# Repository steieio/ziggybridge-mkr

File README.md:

# Ziggy Bridge MKR

This is an adapter for boards in the Arduino MKR form factor, like some of the great low-cost FPGA boards from Trenz.

All of the 100mil pitch connectors use staggered footprints for friction fit so you can use the board without soldering.

This board adapts the MKR dual inline headers to the following connection standards:

 * 2x PMOD
 * mikroBUS Click
 * qwiic/Stemma-QT
 * Raspberry Pi UART

One of the PMOD connectors is issolated on pins D0-D7, the other is connected in parallel with the click/qwiic/uart connectors.

[Click here to view in Kicanvas](https://kicanvas.org/?github=https%3A%2F%2Fgithub.com%2Fsteieio%2Fziggybridge-mkr)

[Click here to purchase from OSH Park](https://oshpark.com/shared_projects/fBhDnFxY)

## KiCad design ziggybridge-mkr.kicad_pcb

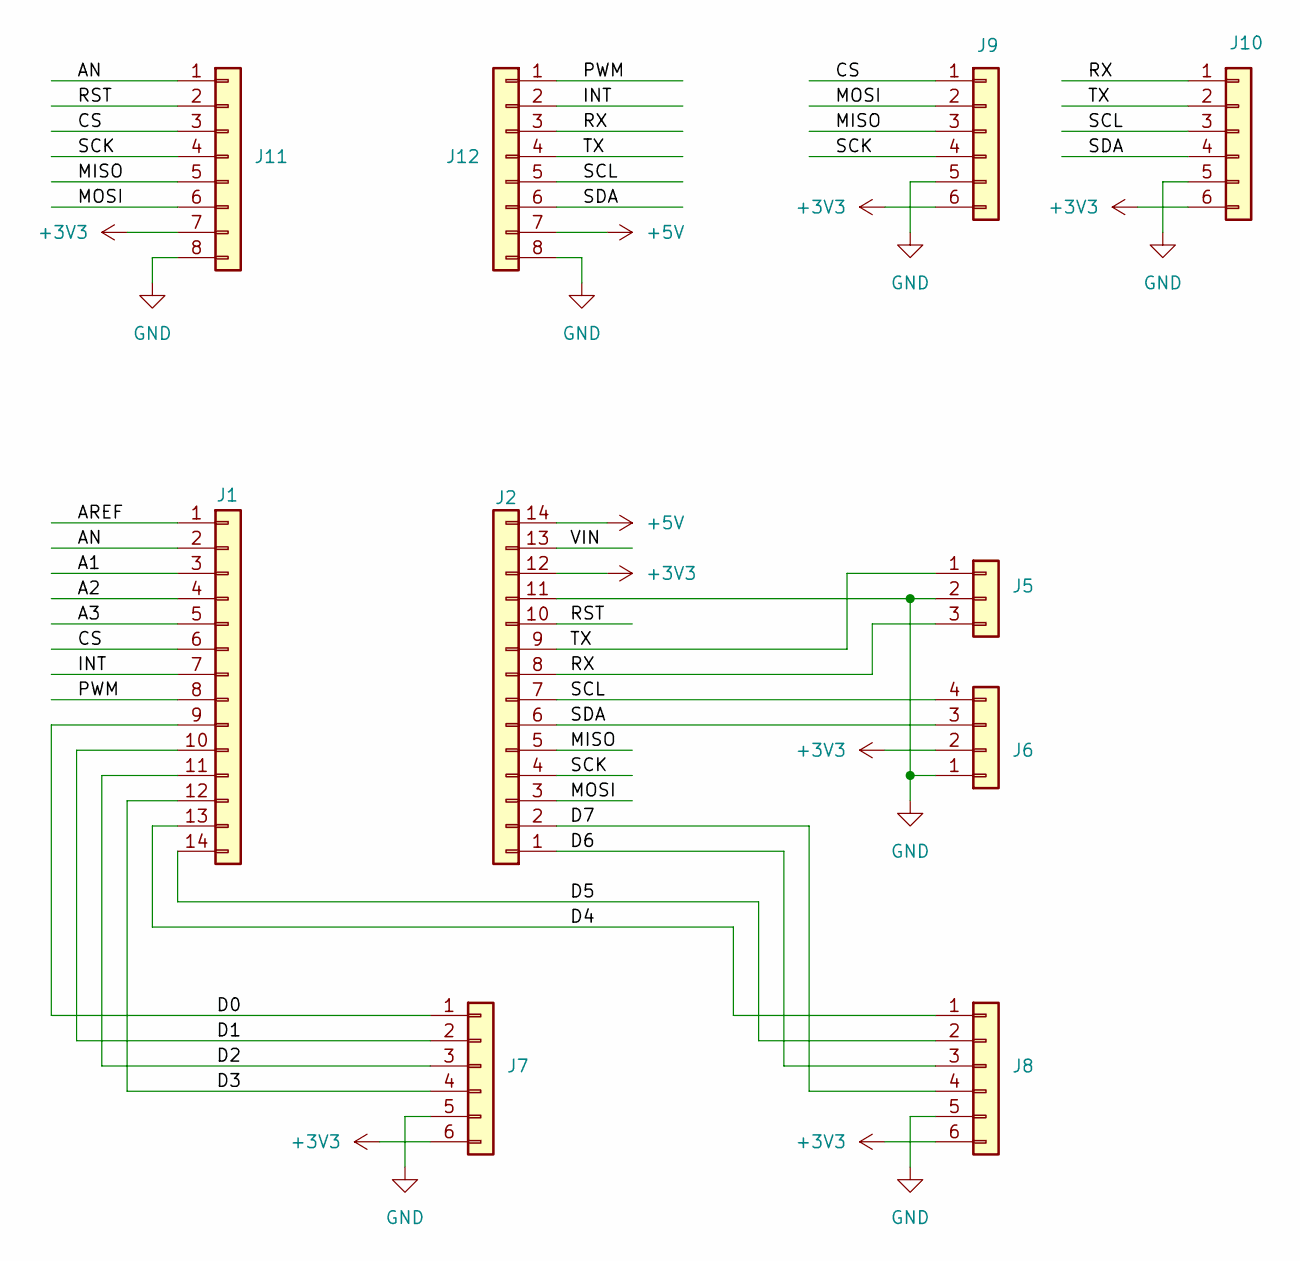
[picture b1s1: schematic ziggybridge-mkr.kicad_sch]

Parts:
J1, J2: Conn_01x14; PinHeader_1x14_P2.54mm_Staggered
J5: Conn_01x03; JST_SH_SM03B-SRSS-TB_1x03-1MP_P1.00mm_Horizontal
J6: Conn_01x04; JST_SH_SM04B-SRSS-TB_1x04-1MP_P1.00mm_Horizontal
J7, J8, J9, J10: Conn_01x06; PinHeader_1x06_P2.54mm_Staggered
J11, J12: Conn_01x08; PinHeader_1x08_P2.54mm_Staggered

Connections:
+3V3: J2.12, J6.2, J7.6, J8.6, J9.6, J10.6, J11.7
+5V: J2.14, J12.7
/A1: J1.3
/A2: J1.4
/A3: J1.5
/AN: J1.2, J11.1
/AREF: J1.1
/CS: J1.6, J9.1, J11.3
/D0: J1.9, J7.1
/D1: J1.10, J7.2
/D2: J1.11, J7.3
/D3: J1.12, J7.4
/D4: J1.13, J8.1
/D5: J1.14, J8.2
/D6: J2.1, J8.3
/D7: J2.2, J8.4
/INT: J1.7, J12.2
/MISO: J2.5, J9.3, J11.5
/MOSI: J2.3, J9.2, J11.6
/PWM: J1.8, J12.1
/RST: J2.10, J11.2
/RX: J2.8, J5.3, J10.1, J12.3
/SCK: J2.4, J9.4, J11.4
/SCL: J2.7, J6.4, J10.3, J12.5
/SDA: J2.6, J6.3, J10.4, J12.6
/TX: J2.9, J5.1, J10.2, J12.4
/VIN: J2.13
GND: J2.11, J5.2, J6.1, J7.5, J8.5, J9.5, J10.5, J11.8, J12.8

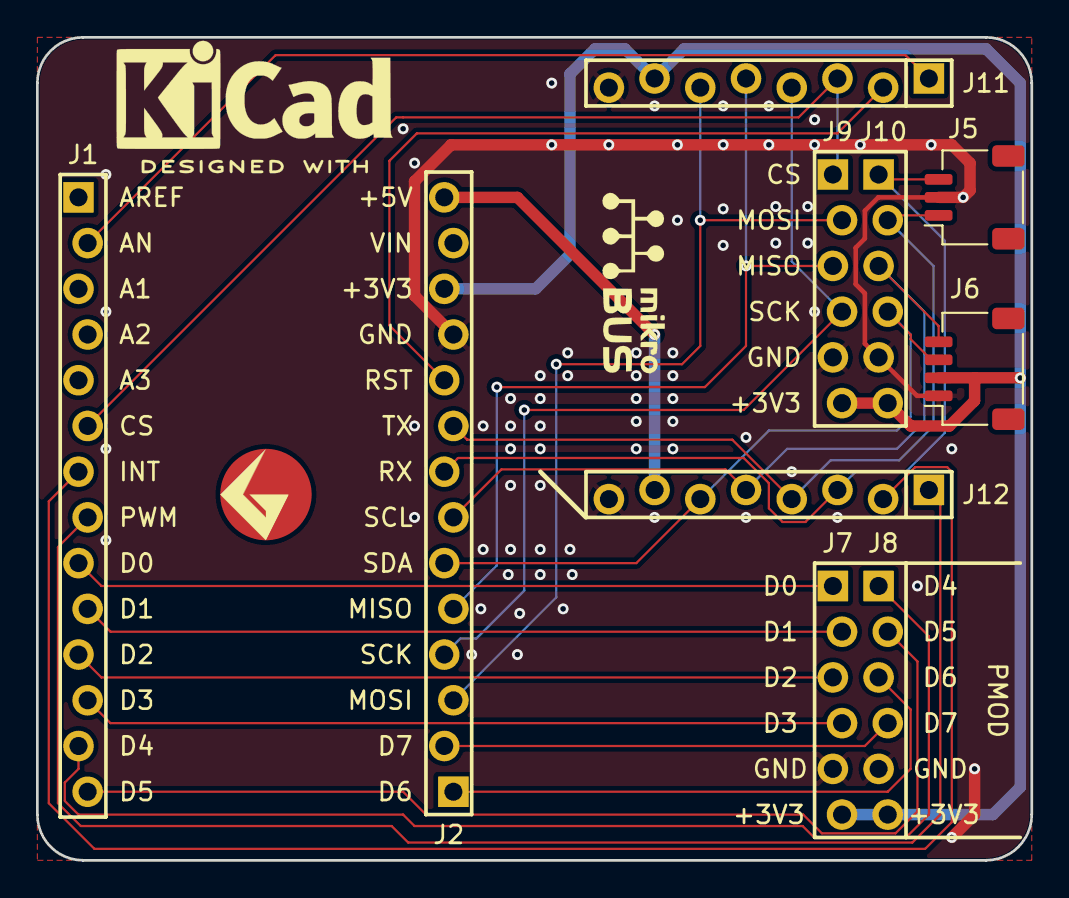
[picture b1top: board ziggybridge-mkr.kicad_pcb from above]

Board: 2 copper layers, 55.2 x 45.7 mm, 11 parts (0 on the bottom side), 23 nets.

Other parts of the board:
GS1: GS_logo; gs_logo_200mil

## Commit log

2025-07-30 chekcing in fully routed board
2025-07-30 fixed labels on MKR socket
2025-07-30 changed to 2 layers
2025-07-30 fixed images in README
2025-08-21 cleaned up design, removed soldermask adjustments and wide ground traces that were defeating thermal releifs
2025-08-21 updated images and added kicanvas iframe to README
2025-08-21 changed iframe to link for Kicanvas
2025-08-21 fixed link
2025-08-21 added OSH Park link
